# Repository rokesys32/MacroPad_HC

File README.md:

Hi , Here's My HackPad For The Blueprint Course , Hope You like it ! :

In That Repository , You'll Find all the Files Needed , 
and if not , you can contact me on slack or at rokesys32dev@gmail.com

> [!NOTE]
> Here's The <b>BOM</b> for parts needed :

```c
◉ 6 MX Cherry Switches
◉ 6 MX Cherry KeyCaps ( r1_100 )
◉ 4 inserts size M3x5mx4mm
◉ 4 Screws Size M3x16mm
◉ 0.91 inch OLED displays
◉ 3D Printed Bottom And Top Case Parts
◉ 4 Pin Header Female ( NOT INCLUDED IN THE COURSE )
◉ 1 XIAO RP2040 ( Mounted As SMD here )
```
Here Are All The Pics Asked By Hack.Club :

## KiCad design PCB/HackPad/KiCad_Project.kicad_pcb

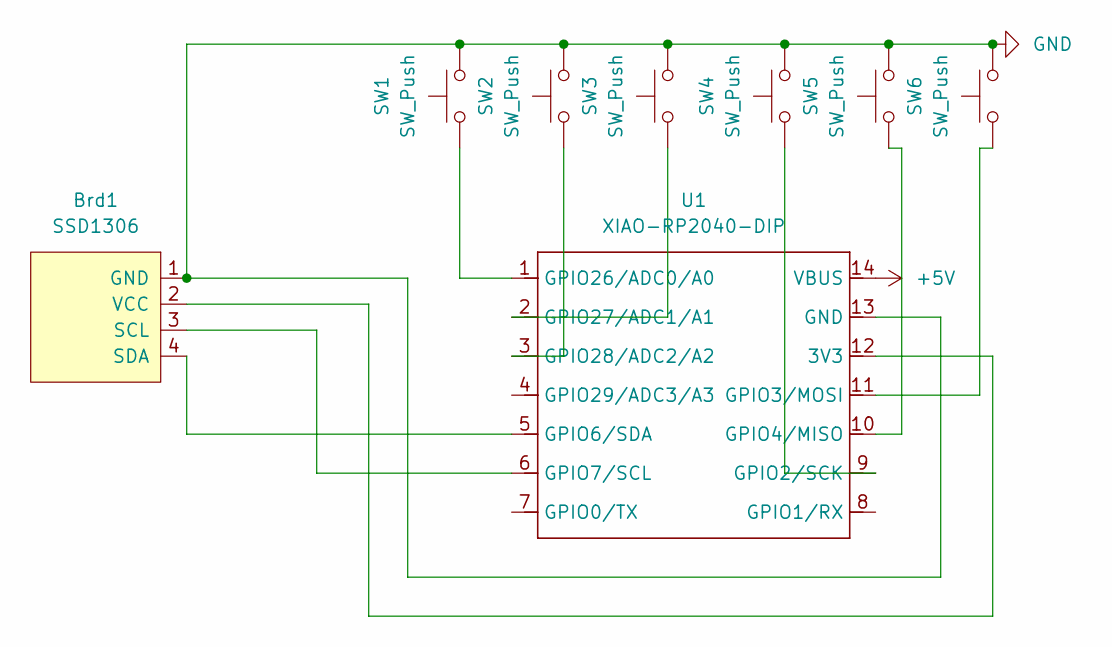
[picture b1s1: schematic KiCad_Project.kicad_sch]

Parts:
Brd1: SSD1306; SSD1306-0.91-OLED-4pin-128x32
SW1, SW2, SW3, SW4, SW5, SW6: SW_Push; SW_Cherry_MX_1.00u3D_PCB
U1: XIAO-RP2040-DIP; XIAO-RP2040-SMD

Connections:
+5V: U1.14 (VBUS)
GND: Brd1.1 (GND), SW1.2, SW2.2, SW3.2, SW4.2, SW5.2, SW6.2, U1.13 (GND)
unnamed: Brd1.3 (SCL), U1.6 (GPIO7/SCL)
unnamed: Brd1.4 (SDA), U1.5 (GPIO6/SDA)
unnamed: Brd1.2 (VCC), U1.12 (3V3)
unnamed: SW4.1, U1.9 (GPIO2/SCK)
unnamed: SW6.1, U1.11 (GPIO3/MOSI)
unnamed: SW5.1, U1.10 (GPIO4/MISO)
unnamed: SW1.1, U1.1 (GPIO26/ADC0/A0)
unnamed: SW3.1, U1.2 (GPIO27/ADC1/A1)
unnamed: SW2.1, U1.3 (GPIO28/ADC2/A2)

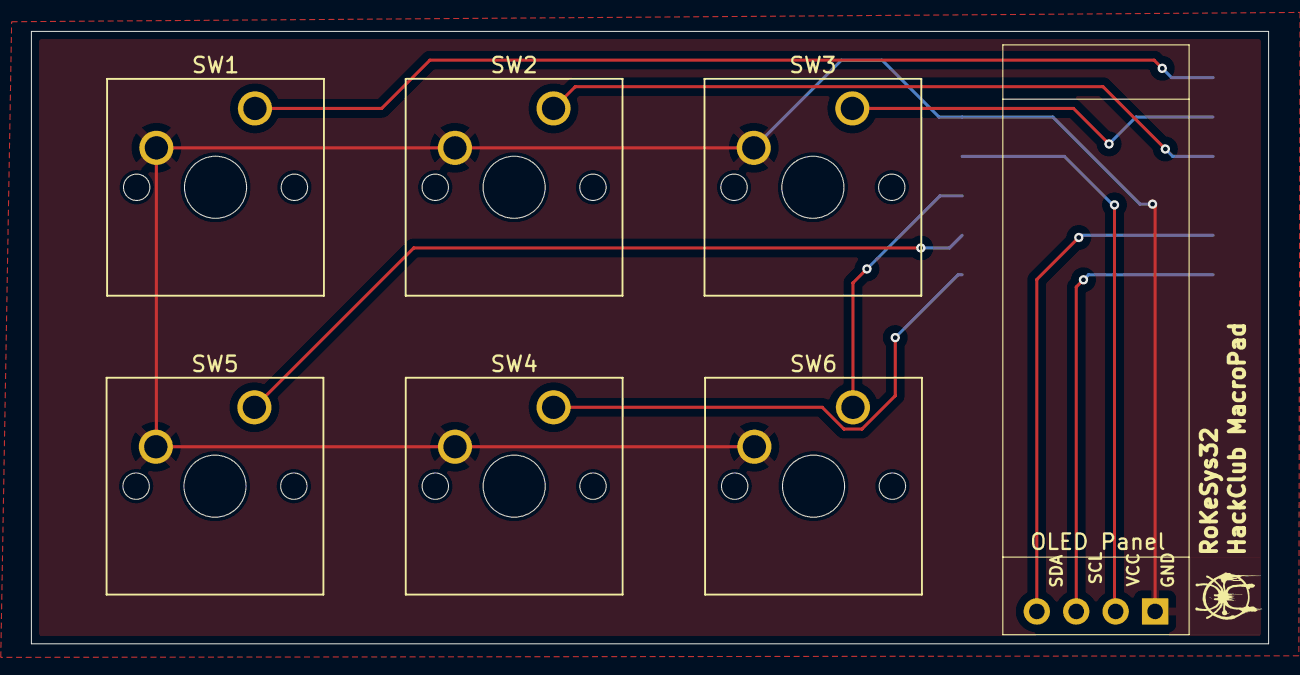
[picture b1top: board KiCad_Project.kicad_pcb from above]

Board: 2 copper layers, 79.7 x 39.5 mm, 8 parts (1 on the bottom side), 10 nets.

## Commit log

2026-01-03 Created README.md
2026-01-03 Updated Bottom With 4 Semi Circle in Corners to maintain board in place
2026-01-03 Update With Semi Circle Also
2026-01-03 Rename overhallpcb.png to overallpcb.png
2026-01-03 Rename overhall.png to overall.png
2026-01-03 Rename overhallpcbback.png to overallpcbback.png
